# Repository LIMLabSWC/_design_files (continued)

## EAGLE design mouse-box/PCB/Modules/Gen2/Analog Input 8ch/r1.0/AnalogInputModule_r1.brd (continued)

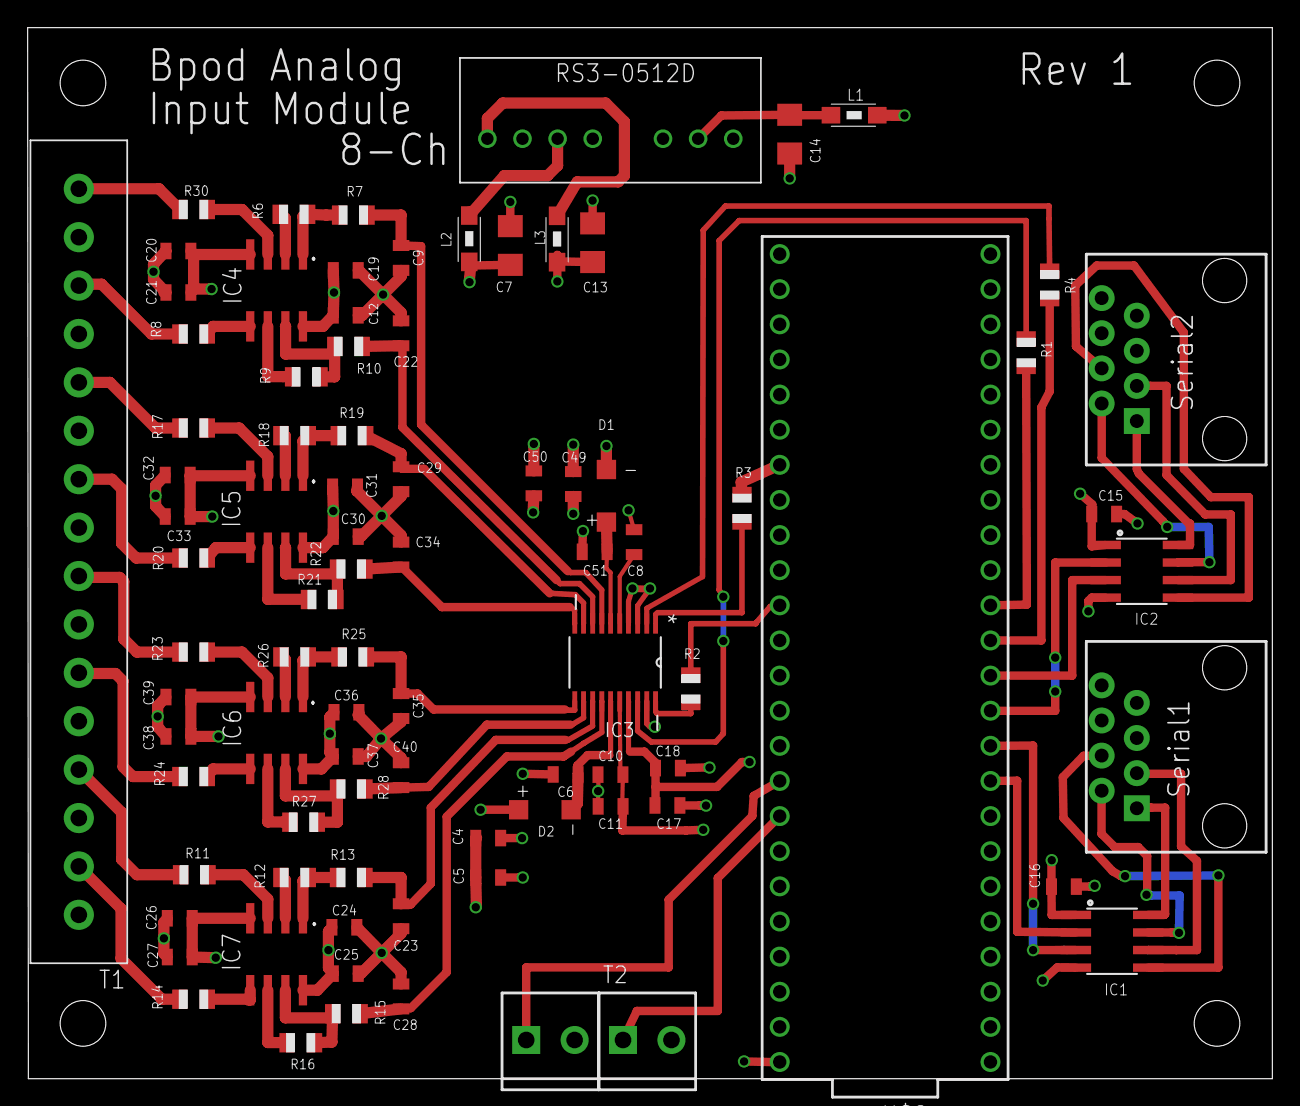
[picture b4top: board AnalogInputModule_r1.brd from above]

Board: 4 copper layers, 90.0 x 76.0 mm, 92 parts (0 on the bottom side), 74 nets.

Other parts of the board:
U$5, U$6, U$7, U$8: STAND-OFF

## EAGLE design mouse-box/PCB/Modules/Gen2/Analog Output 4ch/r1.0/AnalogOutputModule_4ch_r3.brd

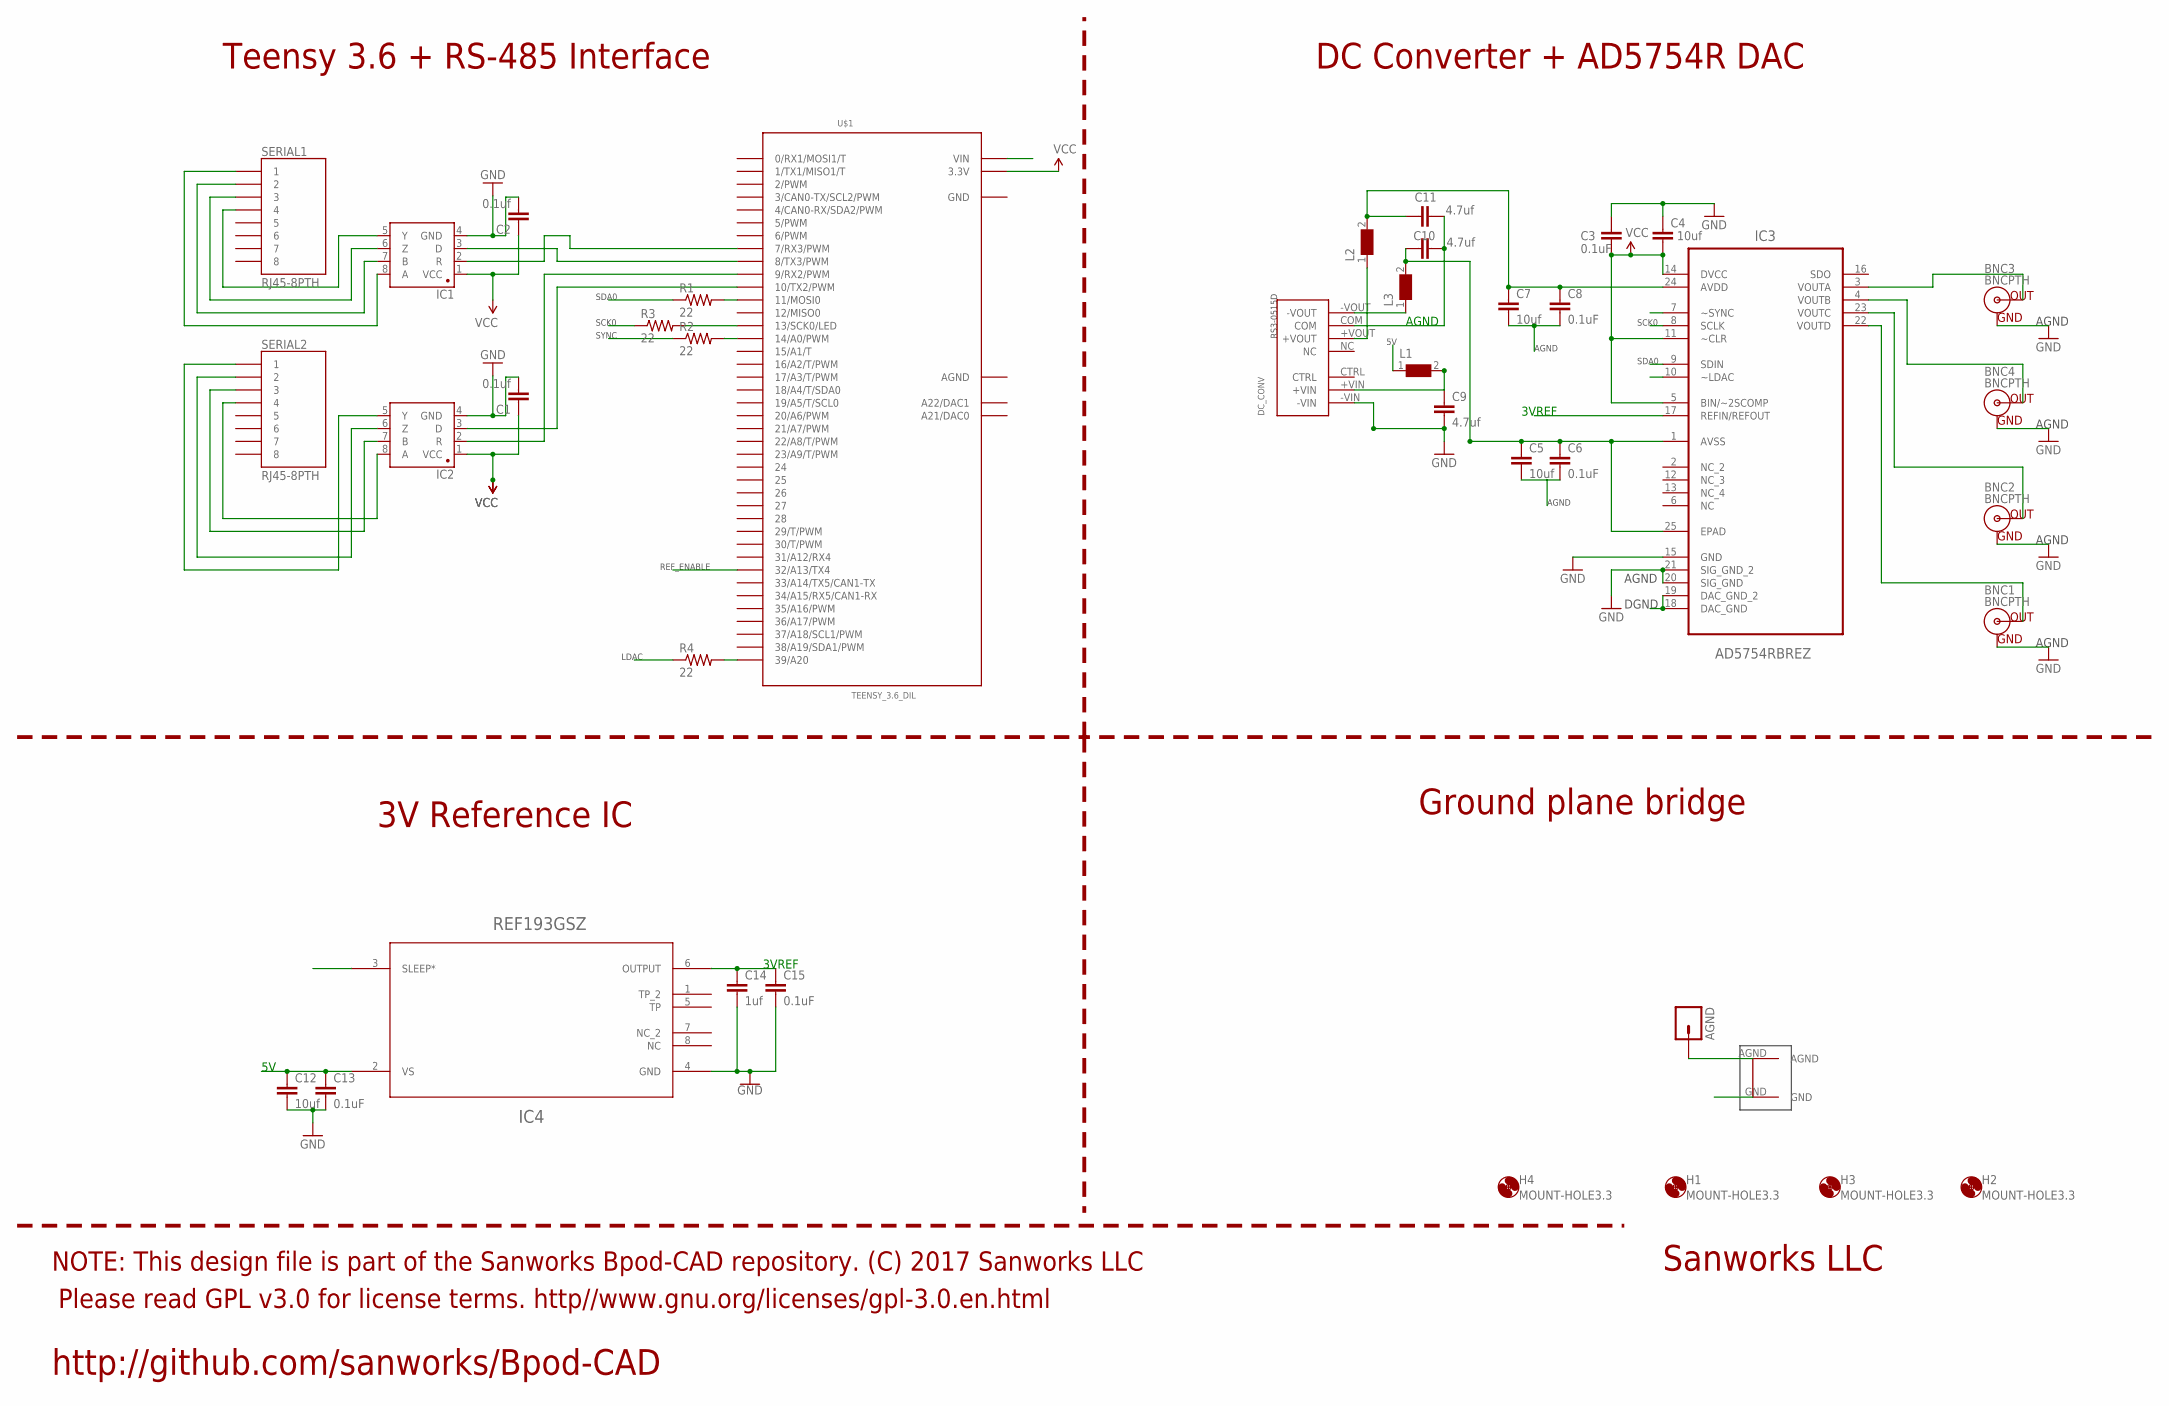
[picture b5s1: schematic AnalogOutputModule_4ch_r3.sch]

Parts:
AGND: M01PTH; 1X01
BNC1, BNC2, BNC3, BNC4: BNCPTH; BNC
C1, C2: 0.1uf; 1206@1
C3, C6, C8, C13, C15: 0.1uF; 0805
C4, C5, C7, C12: 10uf; 1206@1
C9, C10, C11: 4.7uf; 1206@1
C14: 1uf; 1206@1
DC_CONV: RS3-0515D
H1, H2, H3, H4: MOUNT-HOLE3.3; 3,3
IC1, IC2: SN65HVD31DR; SO08
IC3: AD5754RBREZ; SOP65P640X120-25N
IC4: REF193GSZ; R_8
L1, L2, L3: WE-CBF-742792118_1206; 1206
R1, R2, R3, R4: 22; 1206
SERIAL1, SERIAL2: RJ45-8PTH; RJ45-8
U$1: TEENSY_3.6_DIL
U$6: GNDPLANESHRT

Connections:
3VREF: C14.1, C15.1, IC3.17 (REFIN/REFOUT), IC4.6 (OUTPUT)
5V: C3.2, C4.2, C12.1, C13.1, IC3.5 (BIN/~2SCOMP), IC3.11 (~CLR), IC3.14 (DVCC), IC4.2 (VS), L1.1, U$1.VIN
AGND: AGND.1, BNC1.GND, BNC2.GND, BNC3.GND, BNC4.GND, C5.2, C6.2, C7.2, C8.2, C10.1, C11.2, DC_CONV.COM, IC3.18 (DAC_GND), IC3.19 (DAC_GND_2), IC3.20 (SIG_GND), IC3.21 (SIG_GND_2), U$1.AGND, U$6.AGND
GND: C1.2, C2.2, C3.1, C4.1, C9.2, C12.2, C13.2, C14.2, C15.2, DC_CONV.-VIN, IC1.4 (GND), IC2.4 (GND), IC3.15 (GND), IC4.4 (GND), U$1.GND, U$1.GND1 (GND), U$6.GND
LDAC: IC3.10 (~LDAC), R4.1
unnamed: IC1.3 (D), U$1.8 (8/TX3/PWM)
unnamed: IC1.2 (R), U$1.7 (7/RX3/PWM)
unnamed: IC2.8 (A), SERIAL2.4
unnamed: IC2.7 (B), SERIAL2.3
unnamed: IC2.6 (Z), SERIAL2.2
unnamed: IC2.5 (Y), SERIAL2.1
unnamed: IC2.3 (D), U$1.10 (10/TX2/PWM)
unnamed: IC2.2 (R), U$1.9 (9/RX2/PWM)
unnamed: BNC3.S (OUT), IC3.3 (VOUTA)
unnamed: BNC4.S (OUT), IC3.4 (VOUTB)
unnamed: BNC2.S (OUT), IC3.23 (VOUTC)
unnamed: BNC1.S (OUT), IC3.22 (VOUTD)
unnamed: R1.2, U$1.11 (11/MOSI0)
unnamed: R3.2, U$1.13 (13/SCK0/LED)
unnamed: DC_CONV.-VOUT, L3.1
unnamed: DC_CONV.+VOUT, L2.1
unnamed: R2.2, U$1.14/A0 (14/A0/PWM)
unnamed: R4.2, U$1.39/A20
unnamed: IC1.8 (A), SERIAL1.1
unnamed: IC1.7 (B), SERIAL1.2
unnamed: IC1.6 (Z), SERIAL1.3
unnamed: IC1.5 (Y), SERIAL1.4
unnamed: C7.1, C8.1, C10.2, IC3.24 (AVDD), L2.2
unnamed: C9.1, DC_CONV.+VIN, L1.2
REF_ENABLE: IC4.3 (SLEEP*), U$1.32/A13 (32/A13/TX4)
SCK0: IC3.8 (SCLK), R3.1
SDA0: IC3.9 (SDIN), R1.1
SYNC: IC3.7 (~SYNC), R2.1
VCC: C1.1, C2.1, IC1.1 (VCC), IC2.1 (VCC), U$1.3.3V, U$1.3.3V3 (3.3V)
VSS: C5.1, C6.1, C11.1, IC3.1 (AVSS), IC3.25 (EPAD), L3.2

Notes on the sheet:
AGND
SCK0
SDA0
DGND
SYNC
LDAC
3VREF
REF_ENABLE
Teensy 3.6 + RS-485 Interface
DC Converter + AD5754R DAC
3V Reference IC
Ground plane bridge
Please read GPL v3.0 for license terms. http//www.gnu.org/licenses/gpl-3.0.en.html
NOTE: This design file is part of the Sanworks Bpod-CAD repository. (C) 2017 Sanworks LLC
Sanworks LLC
http://github.com/sanworks/Bpod-CAD

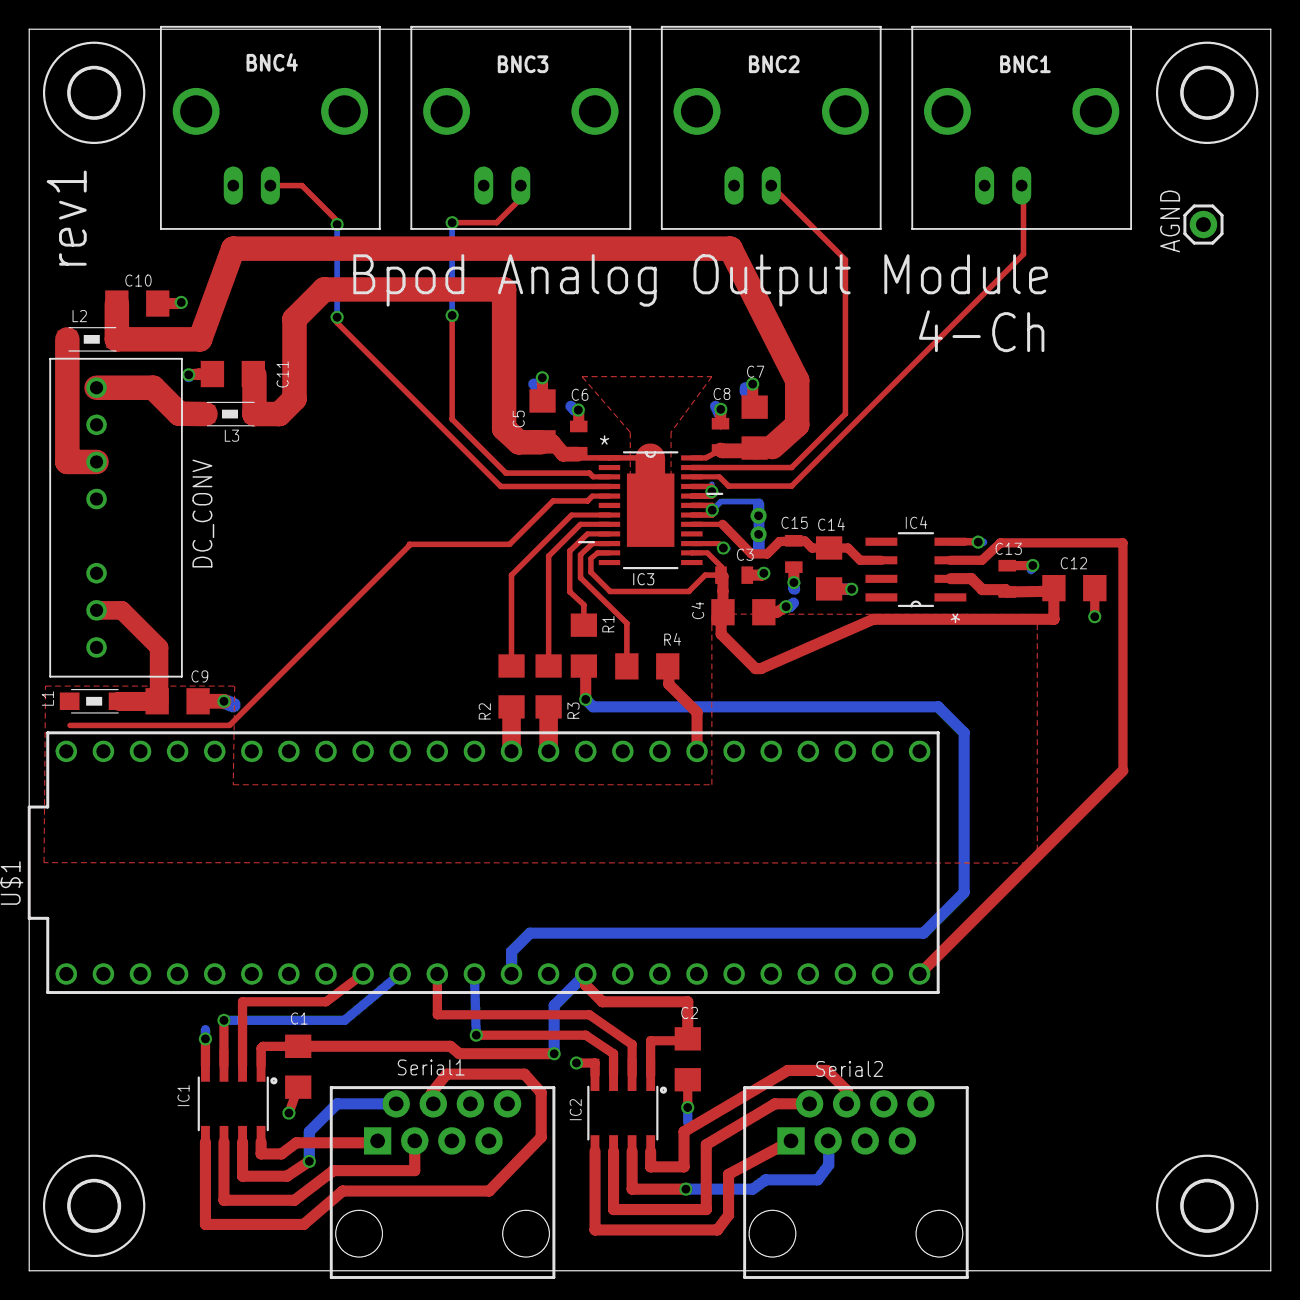
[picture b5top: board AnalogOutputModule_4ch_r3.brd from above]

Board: 2 copper layers, 85.0 x 85.0 mm, 40 parts (0 on the bottom side), 35 nets.
